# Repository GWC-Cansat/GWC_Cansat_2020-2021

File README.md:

# GWC_Cansat_2020-2022
The cansat stuff for 2020 - 2022

https://gwc-cansat.readthedocs.io/en/latest/

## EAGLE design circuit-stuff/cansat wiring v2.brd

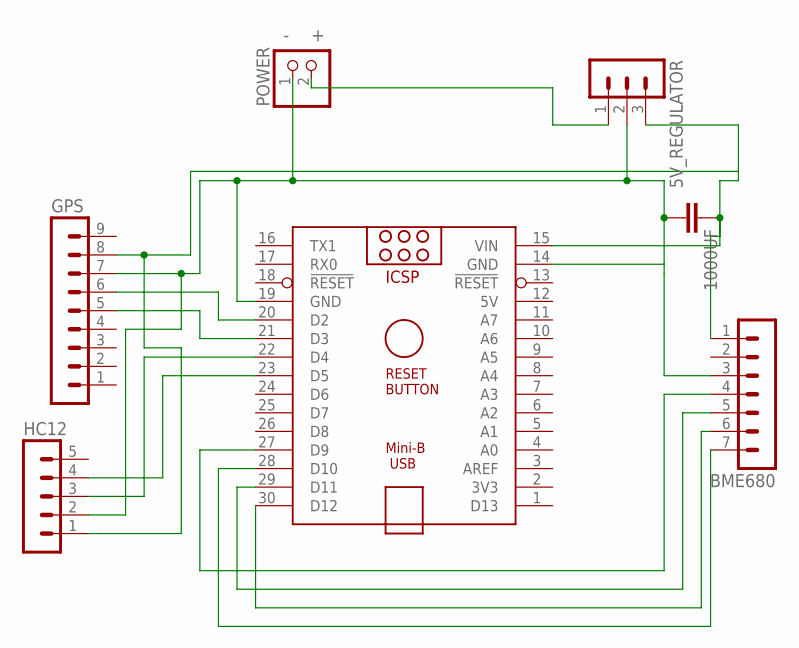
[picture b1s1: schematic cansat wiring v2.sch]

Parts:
5V_REGULATOR: MA03-1
1000UF: C2.5/2; C2.5-2
ARDUINO_NANO1: ARDUINO_NANO
BME680: MA07-1
GPS: MA09-1
HC12: MA05-1
POWER: PINHD-1X2; 1X02

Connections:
5V: ARDUINO_NANO1.12 (5V)
+: 5V_REGULATOR.2, 1000UF.2, ARDUINO_NANO1.14 (GND), ARDUINO_NANO1.19 (GND), BME680.3, GPS.7, HC12.2, POWER.1
-: 5V_REGULATOR.1, POWER.2
unnamed: ARDUINO_NANO1.27 (D9), BME680.4
unnamed: ARDUINO_NANO1.29 (D11), BME680.5
unnamed: ARDUINO_NANO1.20 (D2), GPS.6
unnamed: 5V_REGULATOR.3, 1000UF.1, ARDUINO_NANO1.15 (VIN), BME680.1, GPS.8, HC12.1
unnamed: ARDUINO_NANO1.21 (D3), GPS.5
unnamed: ARDUINO_NANO1.30 (D12), BME680.6
unnamed: ARDUINO_NANO1.23 (D5), HC12.4
unnamed: ARDUINO_NANO1.28 (D10), BME680.7
unnamed: ARDUINO_NANO1.22 (D4), HC12.3

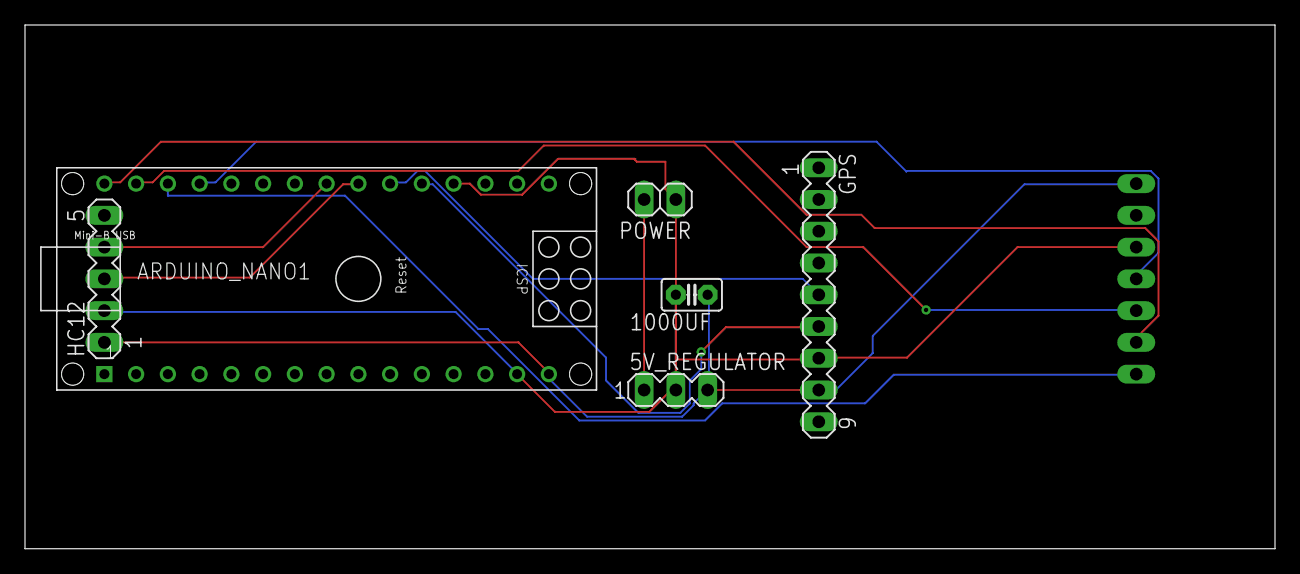
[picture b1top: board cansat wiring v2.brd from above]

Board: 2 copper layers, 100.0 x 41.9 mm, 7 parts (1 on the bottom side), 11 nets.

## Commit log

2020-12-03 Partially working arduino code
2021-06-14 It finally works
2021-07-06 Latest version with fault tolerance
2021-09-14 Added image
2021-09-14 Fixed date
